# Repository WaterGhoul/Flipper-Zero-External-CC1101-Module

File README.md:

# Flipper Zero External CC1101 Module
A universal module to add an external CC1101 modue to the Flipper Zero

# Configuration
This board is by default configured for an EByte CC1101 module, with the jumpers left as-is. These jumper pads are indicated by the surrounding dashed lined rectangle. 

To congfigure the board for a generic CC1101 module, cut the default jumper traces with a knife and bridge the opposite jumper pads, indicated by the surounding solid lined rectangle.

# Purchasing
You can purchase this and my other products on Tindie!

# Donate
Nothing is EVER expected for providing my designs, however if you wish to support my work, you may donate to these addresses.

**ETH** ``0x7C65625d6dac7DC351eEf3C0A21e9f0F4a3B537b``

**BTC** ``bc1q4rn3ceyk42349uuxt2m7mzw4kcewu0e5698fms``

**DOGE** ``DC1Q4ip8mLsAgvbLL4evxJQhaCE7QosFZ9``

**LTC** ``ltc1q33sg6eea2yqzdx85h38v7rpw7kzlgmqtn8m5nm``

# License
<br />This work is licensed under a <a rel="license" href="http://creativecommons.org/licenses/by-sa/4.0/">Creative Commons Attribution-ShareAlike 4.0 International License</a>.

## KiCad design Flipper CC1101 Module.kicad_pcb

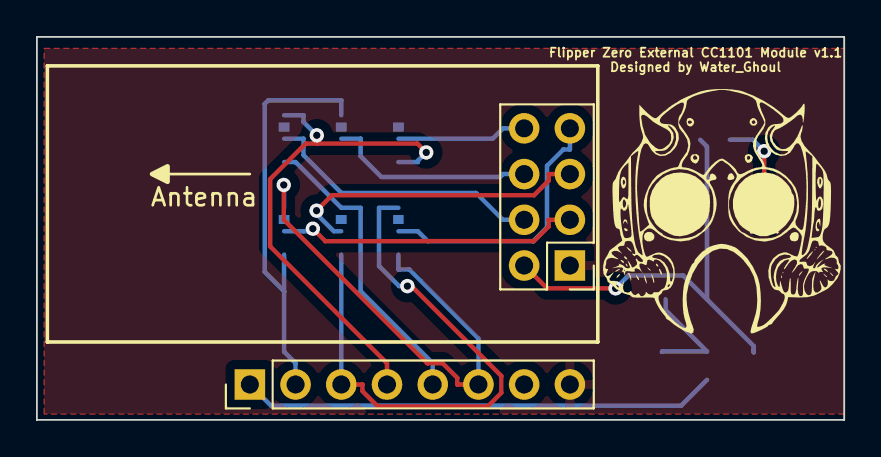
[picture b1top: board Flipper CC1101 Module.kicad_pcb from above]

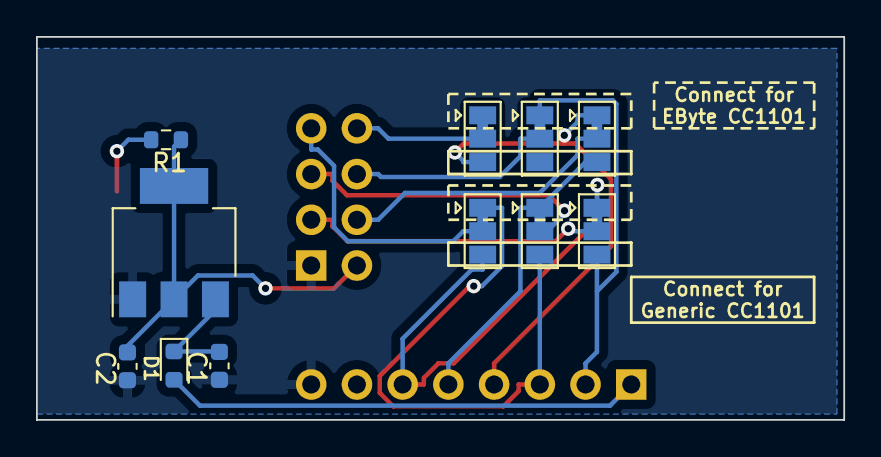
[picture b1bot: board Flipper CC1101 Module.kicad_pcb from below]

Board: 2 copper layers, 44.8 x 21.3 mm, 14 parts (11 on the bottom side), 16 nets.

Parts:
C1: 10uF; C_0603_1608Metric
C2: 100uF; C_0603_1608Metric
D1: 1N4001; D_0603_1608Metric
D2: LED; LED_0603_1608Metric
J1: EByte CC1101; PinHeader_2x04_P2.54mm_Vertical
J3: Conn_01x08; PinHeader_1x08_P2.54mm_Vertical
JP1, JP2, JP3, JP4, JP5, JP6: SolderJumper_3_Bridged12; SolderJumper-3_P1.3mm_Bridged12_Pad1.0x1.5mm
R1: 1k; R_0603_1608Metric
U1: AMS1117CD-3.3; SOT-223-3_TabPin2

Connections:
+3V3: C2.1, J1.2, R1.1, U1.2 (VO)
+5V: D1.2 (A), J3.1
CS: J3.4, JP2.1 (A), JP5.3 (B)
GD0: J3.6, JP1.1 (A), JP6.3 (B)
GND: C1.2, C2.2, D2.1 (K), J1.1, J3.8, U1.1 (GND)
MISO: J3.3, JP3.3 (B), JP6.1 (A)
MOSI: J3.2, JP1.3 (B), JP4.1 (A)
unnamed: C1.1, D1.1 (K), U1.3 (VI)
unnamed: D2.2 (A), R1.2
PIN3: J1.3, JP1.2 (C)
PIN4: J1.4, JP2.2 (C)
PIN5: J1.5, JP3.2 (C)
PIN6: J1.6, JP4.2 (C)
PIN7: J1.7, JP6.2 (C)
PIN8: J1.8, JP5.2 (C)
SCK: J3.5, JP2.3 (B), JP3.1 (A)

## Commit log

2023-09-18 Update README.md
    Added TODO
2023-09-18 Add files via upload
    Added KiCAD source files
2023-09-18 Add KiCAD Project file
2023-09-19 Added License
2023-09-21 Added Images
    Added images showing the default EByte module configuration of the jumpers and the optional cut and soldered configuration of the jumpers for a generic module.
2023-09-21 Update README.md
    Added configuration images
    \
